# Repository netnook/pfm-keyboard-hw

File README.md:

# PFM keyboard

This repo contains the hardware design for the PFM (Perfect For Me) keyboard.
This is a 38 key split keyboard which - as hinted by the name - is designed specifically for me, 
my hands, my typing habits and so on. 

**Outline**

In particular: 
- it has a relatively strong stagger
- the inner most index finger colum has only two keys
- the top most keys of the pinky column are actually used with the ring fingers (those keys are 
spaced a little further up)
- the outer most columns have only one key for the pinky to find.  

Together this reduces overstretching leading to better comfort and reduces the need for hand movement and my tendency to loose my home position when I do so.
Despite the name, it is still not perfect.

*Note: I actually don't use the fourth (lowest) key in the middle finger column - my middle finger does not seem to be able to memorize 2 different downward 
travel distances - and it will likely be removed in a future version.*

The keyboard is based on the [frood microcontroller](https://42keebs.eu/shop/parts/controllers/frood-rp2040-pro-micro-controller/) which allows the use of 38 keys without any diodes.

The board uses MX keys both with hot-swap sockets or directly soldered.

QMK based firmware for this board is available in the [pfm-keyboard-fw](https://github.com/netnook/pfm-keyboard-fw) repo.

## Schematic

[Schematic as PDF](/assets/schematic.pdf)

## Parts

- 2x [frood microcontroller](https://42keebs.eu/shop/parts/controllers/frood-rp2040-pro-micro-controller/)
- sockets for MCU (optional)
- OLED display (link ?)
- sockets for display (this also allows bridging the distance required to allow the display to lay above the mcu - long pins could be used instead)
- 38x MX switches and keycaps of choice 
- 38x MX sockets - (optional - PCB can be used with or without sockets)
- 1 or 2 reset switches such as [this](https://42keebs.eu/shop/parts/components/reset-switch/?attribute_type=Through-hole%202-pin%206x3&attribute_pa_colour=black) - (optional - right hand side only needs programming once and the tiny reset switch on the mcu does the job, for the left hand side which is re-programmed with every layout change the switch is convenient to have)
- piezo buzzer (source ?)
- 2x TRRS socket such as [this](https://42keebs.eu/shop/parts/components/pj-320-trrs-socket/?attribute_type=PJ-320A%20(Through-Hole)&attribute_pa_colour=black)
- 1x TRRS or TRS cable
- USB cable for connection to PC
- rubber feet (8mm diameter, at least 2mm thick - preferably 3mm thick)

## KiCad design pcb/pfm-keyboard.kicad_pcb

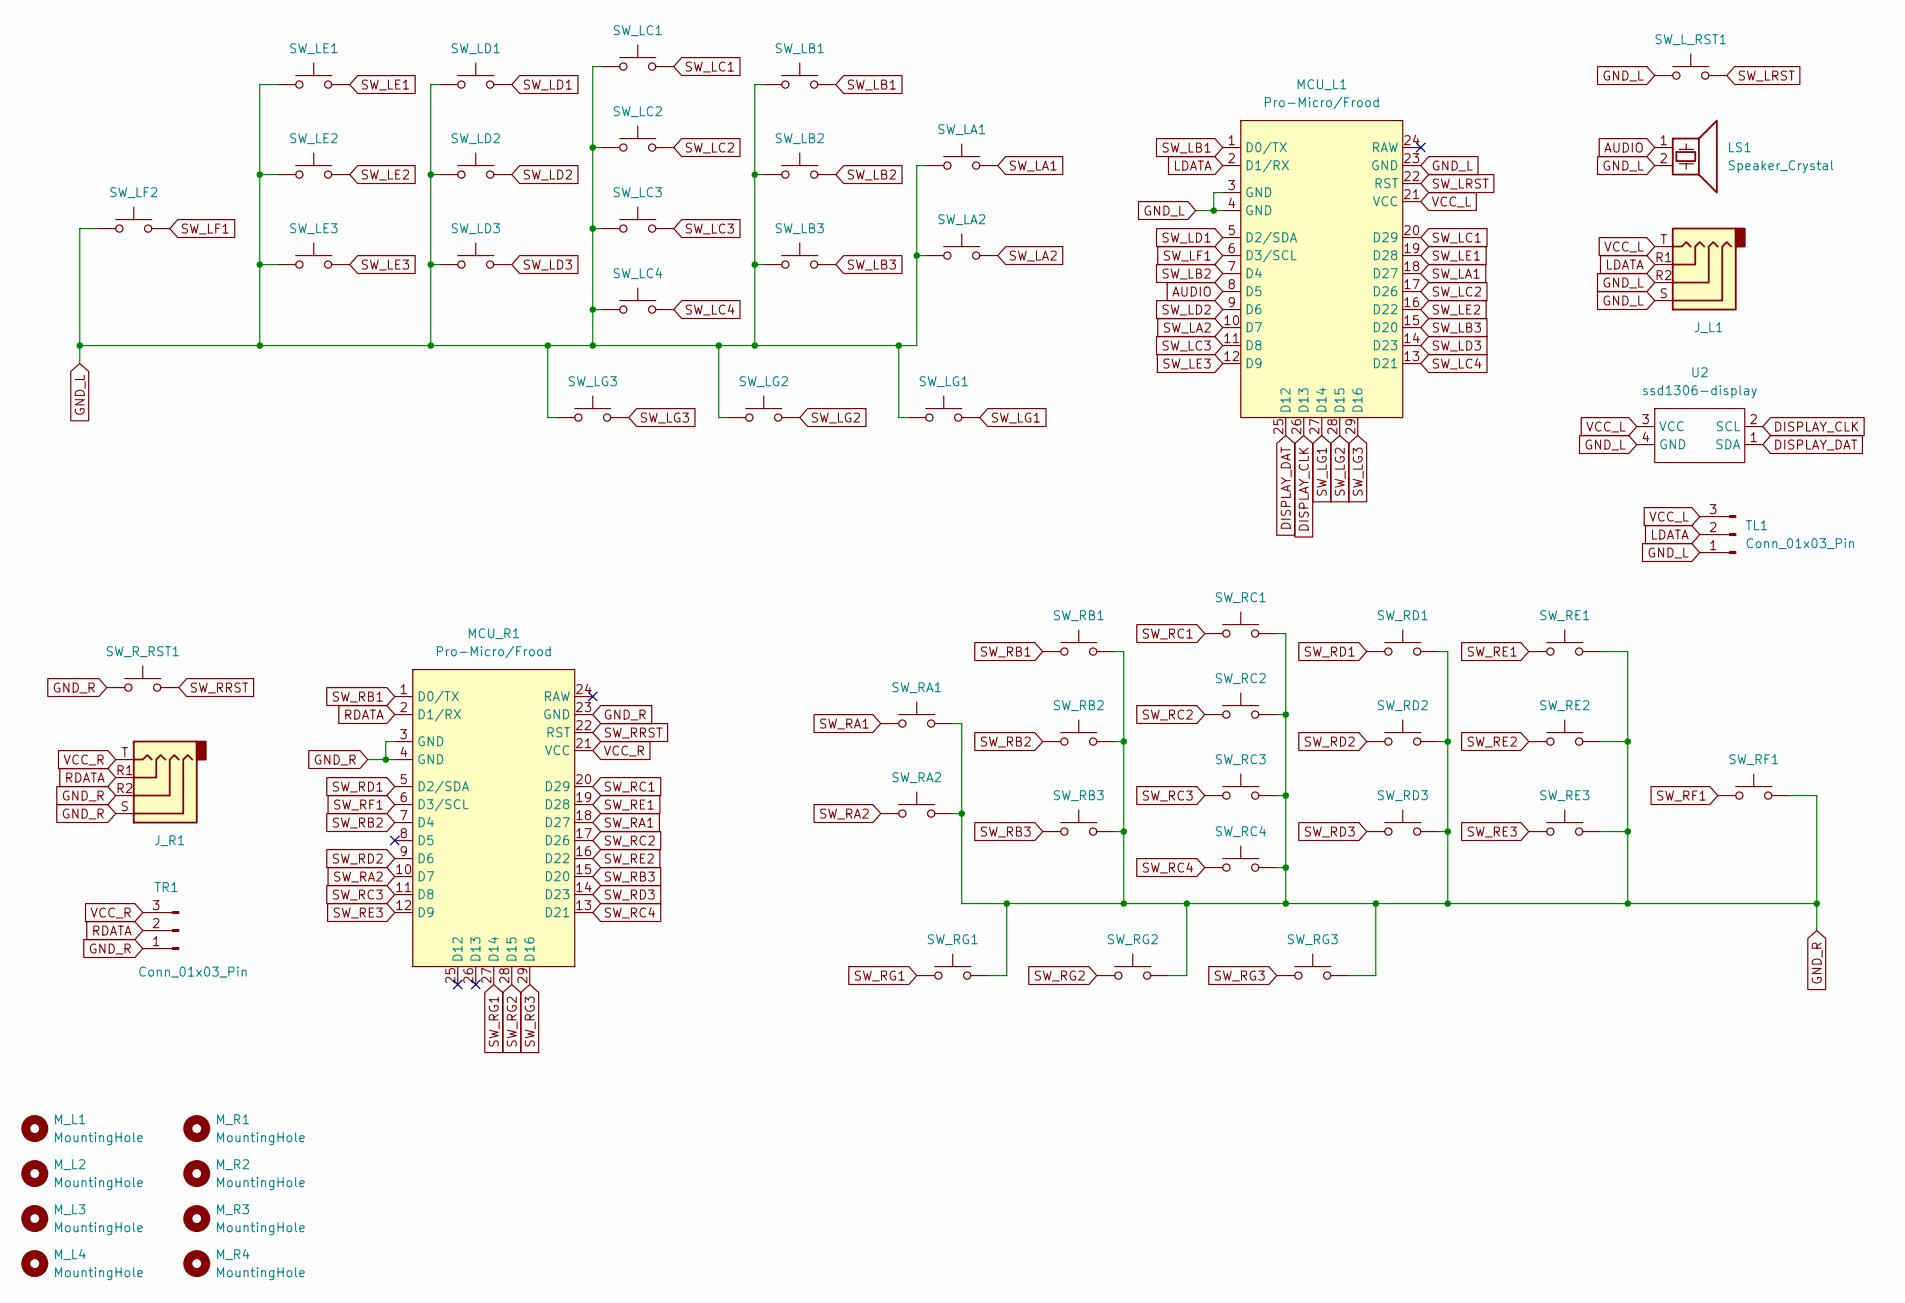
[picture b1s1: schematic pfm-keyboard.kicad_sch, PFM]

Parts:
J_L1: AudioJack4; trrs-socket
J_R1: AudioJack4; trrs-socket
LS1: Speaker_Crystal; buzzer-12x8.2-6.6
MCU_L1: Pro-Micro/Frood; frood
MCU_R1: Pro-Micro/Frood; frood
M_L1, M_L2, M_L3, M_L4: MountingHole; MountingHole_2.7mm_M2.5
M_R1, M_R2, M_R3, M_R4: MountingHole; MountingHole_2.7mm_M2.5
SW_LA1, SW_LA2: SW_Push; mx-socket-hs-and-solder
SW_LB1, SW_LB2, SW_LB3: SW_Push; mx-socket-hs-and-solder
SW_LC1, SW_LC2, SW_LC3, SW_LC4: SW_Push; mx-socket-hs-and-solder
SW_LD1, SW_LD2, SW_LD3: SW_Push; mx-socket-hs-and-solder
SW_LE1, SW_LE2, SW_LE3: SW_Push; mx-socket-hs-and-solder
SW_LF2: SW_Push; mx-socket-hs-and-solder
SW_LG1, SW_LG2, SW_LG3: SW_Push; mx-socket-hs-and-solder
SW_L_RST1: SW_Push; reset-switch
SW_RA1, SW_RA2: SW_Push; mx-socket-hs-and-solder
SW_RB1, SW_RB2, SW_RB3: SW_Push; mx-socket-hs-and-solder
SW_RC1, SW_RC2, SW_RC3, SW_RC4: SW_Push; mx-socket-hs-and-solder
SW_RD1, SW_RD2, SW_RD3: SW_Push; mx-socket-hs-and-solder
SW_RE1, SW_RE2, SW_RE3: SW_Push; mx-socket-hs-and-solder
SW_RF1: SW_Push; mx-socket-hs-and-solder
SW_RG1, SW_RG2, SW_RG3: SW_Push; mx-socket-hs-and-solder
SW_R_RST1: SW_Push; reset-switch
TL1: Conn_01x03_Pin; PinHeader_1x03_P2.54mm_Vertical
TR1: Conn_01x03_Pin; PinHeader_1x03_P2.54mm_Vertical
U2: ssd1306-display; display-128x32

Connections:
AUDIO: LS1.1, MCU_L1.8 (D5)
DISPLAY_CLK: MCU_L1.26 (D13), U2.2 (SCL)
DISPLAY_DAT: MCU_L1.25 (D12), U2.1 (SDA)
GND_L: J_L1.R2, J_L1.S, LS1.2, MCU_L1.3 (GND), MCU_L1.4 (GND), MCU_L1.23 (GND), SW_LA1.2, SW_LA2.2, SW_LB1.2, SW_LB2.2, SW_LB3.2, SW_LC1.2, SW_LC2.2, SW_LC3.2, SW_LC4.2, SW_LD1.2, SW_LD2.2, SW_LD3.2, SW_LE1.2, SW_LE2.2, SW_LE3.2, SW_LF2.2, SW_LG1.1, SW_LG2.1, SW_LG3.2, SW_L_RST1.1, TL1.1, U2.4 (GND)
GND_R: J_R1.R2, J_R1.S, MCU_R1.3 (GND), MCU_R1.4 (GND), MCU_R1.23 (GND), SW_RA1.1, SW_RA2.1, SW_RB1.1, SW_RB2.1, SW_RB3.1, SW_RC1.1, SW_RC2.1, SW_RC3.1, SW_RC4.1, SW_RD1.1, SW_RD2.1, SW_RD3.1, SW_RE1.1, SW_RE2.1, SW_RE3.1, SW_RF1.1, SW_RG1.2, SW_RG2.2, SW_RG3.1, SW_R_RST1.2, TR1.1
LDATA: J_L1.R1, MCU_L1.2 (D1/RX), TL1.2
RDATA: J_R1.R1, MCU_R1.2 (D1/RX), TR1.2
SW_LA1: MCU_L1.18 (D27), SW_LA1.1
SW_LA2: MCU_L1.10 (D7), SW_LA2.1
SW_LB1: MCU_L1.1 (D0/TX), SW_LB1.1
SW_LB2: MCU_L1.7 (D4), SW_LB2.1
SW_LB3: MCU_L1.15 (D20), SW_LB3.1
SW_LC1: MCU_L1.20 (D29), SW_LC1.1
SW_LC2: MCU_L1.17 (D26), SW_LC2.1
SW_LC3: MCU_L1.11 (D8), SW_LC3.1
SW_LC4: MCU_L1.13 (D21), SW_LC4.1
SW_LD1: MCU_L1.5 (D2/SDA), SW_LD1.1
SW_LD2: MCU_L1.9 (D6), SW_LD2.1
SW_LD3: MCU_L1.14 (D23), SW_LD3.1
SW_LE1: MCU_L1.19 (D28), SW_LE1.1
SW_LE2: MCU_L1.16 (D22), SW_LE2.1
SW_LE3: MCU_L1.12 (D9), SW_LE3.1
SW_LF1: MCU_L1.6 (D3/SCL), SW_LF2.1
SW_LG1: MCU_L1.27 (D14), SW_LG1.2
SW_LG2: MCU_L1.28 (D15), SW_LG2.2
SW_LG3: MCU_L1.29 (D16), SW_LG3.1
SW_LRST: MCU_L1.22 (RST), SW_L_RST1.2
SW_RA1: MCU_R1.18 (D27), SW_RA1.2
SW_RA2: MCU_R1.10 (D7), SW_RA2.2
SW_RB1: MCU_R1.1 (D0/TX), SW_RB1.2
SW_RB2: MCU_R1.7 (D4), SW_RB2.2
SW_RB3: MCU_R1.15 (D20), SW_RB3.2
SW_RC1: MCU_R1.20 (D29), SW_RC1.2
SW_RC2: MCU_R1.17 (D26), SW_RC2.2
SW_RC3: MCU_R1.11 (D8), SW_RC3.2
SW_RC4: MCU_R1.13 (D21), SW_RC4.2
SW_RD1: MCU_R1.5 (D2/SDA), SW_RD1.2
SW_RD2: MCU_R1.9 (D6), SW_RD2.2
SW_RD3: MCU_R1.14 (D23), SW_RD3.2
SW_RE1: MCU_R1.19 (D28), SW_RE1.2
SW_RE2: MCU_R1.16 (D22), SW_RE2.2
SW_RE3: MCU_R1.12 (D9), SW_RE3.2
SW_RF1: MCU_R1.6 (D3/SCL), SW_RF1.2
SW_RG1: MCU_R1.27 (D14), SW_RG1.1
SW_RG2: MCU_R1.28 (D15), SW_RG2.1
SW_RG3: MCU_R1.29 (D16), SW_RG3.2
SW_RRST: MCU_R1.22 (RST), SW_R_RST1.1
VCC_L: J_L1.T, MCU_L1.21 (VCC), TL1.3, U2.3 (VCC)
VCC_R: J_R1.T, MCU_R1.21 (VCC), TR1.3

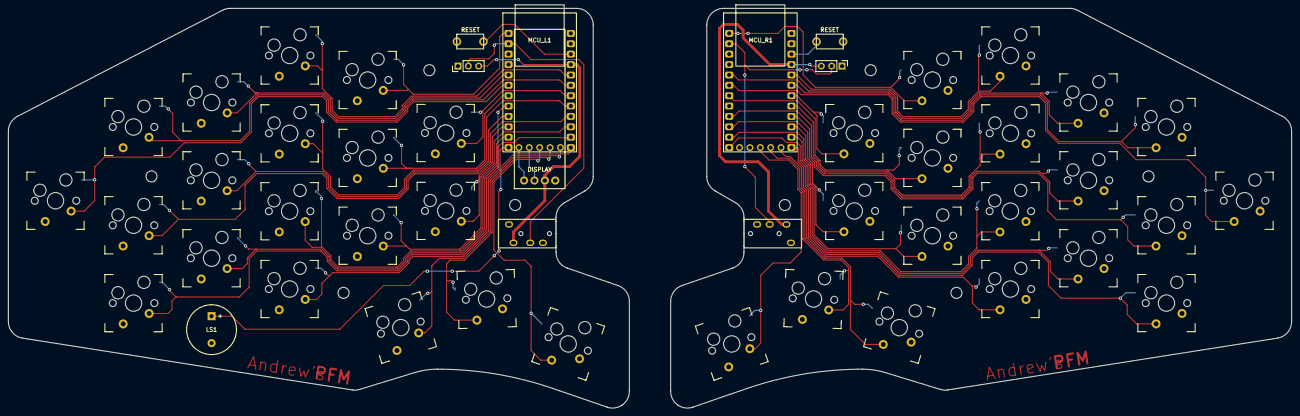
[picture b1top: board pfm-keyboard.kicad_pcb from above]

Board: 2 copper layers, 314.1 x 97.8 mm, 56 parts (0 on the bottom side), 49 nets.

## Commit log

2024-03-03 import cad files
2024-03-03 import kicad files
2024-03-03 switched connections on TRRS jack for compatibility with TRS cables
2024-03-06 Use same MCU pins on left and right to avoid problems when right is master. Added mounting holes to schematic.
2024-03-17 Add TRS connector model and position on board
2024-03-26 Version 4 - better key placement, same pin usage on left and right, added test points
2024-04-15 Added initial readme
2024-04-29 Added test assets to readme
2024-05-01 Added picture and more description.
2024-05-01 Note about removing lowest middle finger key in future.
